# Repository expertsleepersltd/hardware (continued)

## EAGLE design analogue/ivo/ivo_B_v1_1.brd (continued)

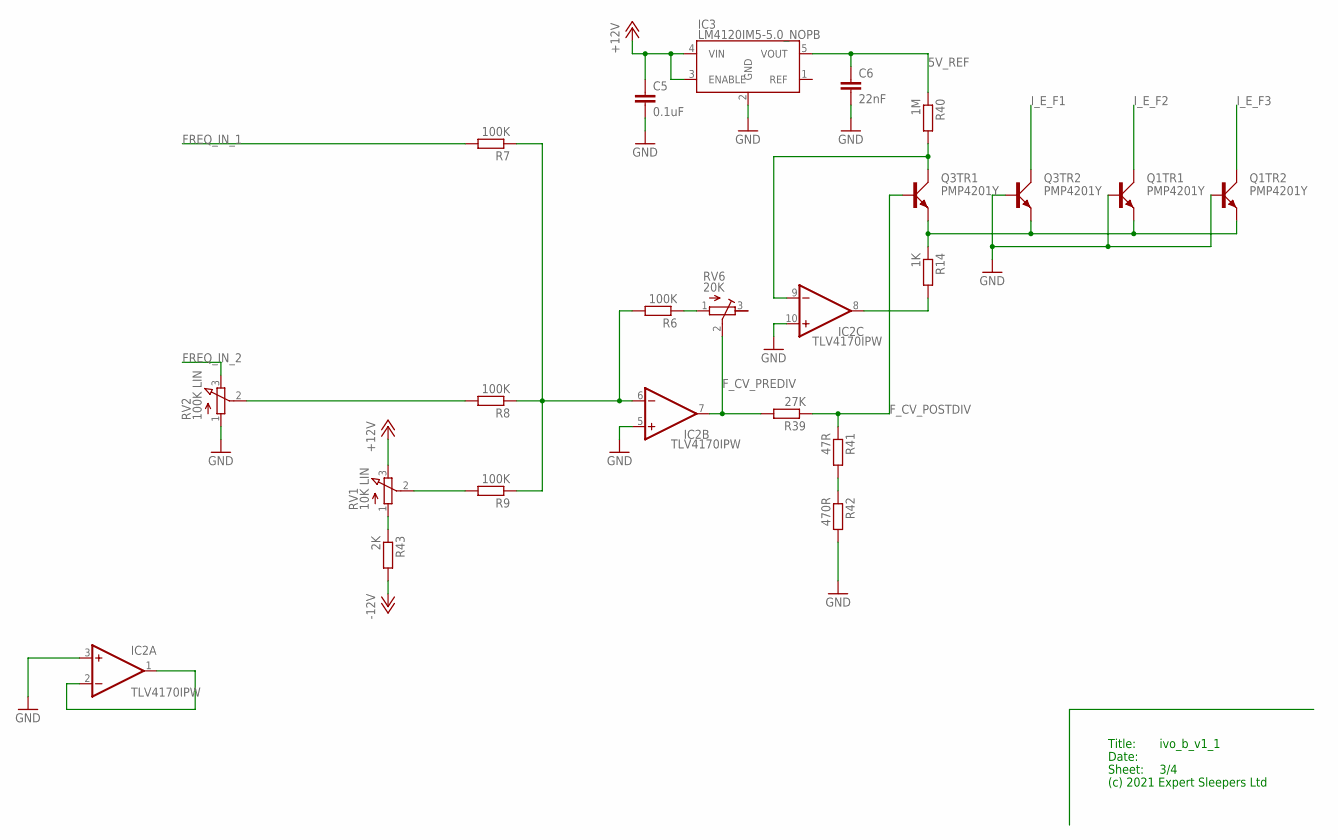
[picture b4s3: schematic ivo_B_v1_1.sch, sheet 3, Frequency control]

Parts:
C5: 0.1uF; C0402
C6: 22nF; C0402
IC2: TLV4170IPW; PW_R-PDSO-G14
IC3: LM4120IM5-5.0_NOPB; SOT95P280X145-5N
Q1, Q3: PMP4201Y; SOT65P210X110-6N
R6, R7, R8, R9: 100K; R0603
R14: 1K; R0603
R39: 27K; R0603
R40: 1M; R0603
R41: 47R; R0603
R42: 470R; R1206
R43: 2K; R0603
RV1: 10K LIN; RD1610NOA0X
RV2: 100K LIN; RD1610NOA0X
RV6: 20K; TC33X

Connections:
5V_REF: C6.1, IC3.5 (VOUT), R40.1
+12V: C5.1, IC3.3 (ENABLE), IC3.4 (VIN), RV1.3 (E); also elsewhere on the board
-12V: R43.2; also elsewhere on the board
FREQ_IN_1: R7.2; also elsewhere on the board
FREQ_IN_2: RV2.3 (E); also elsewhere on the board
F_CV_POSTDIV: Q3.1 (B), R39.1, R41.1
F_CV_PREDIV: IC2.7 (OUT), R39.2, RV6.2 (S)
GND: C5.2, C6.2, IC2.3 (+IN), IC2.5 (+IN), IC2.10 (+IN), IC3.2 (GND), Q1.1 (B), Q1.2 (B), Q3.2 (B), R42.2, RV2.1 (A); also elsewhere on the board
I_E_F1: Q3.3 (C); also elsewhere on the board
I_E_F2: Q1.6 (C); also elsewhere on the board
I_E_F3: Q1.3 (C); also elsewhere on the board
unnamed: R43.1, RV1.1 (A)
unnamed: R6.1, RV6.1 (A)
unnamed: IC2.6 (-IN), R6.2, R7.1, R8.1, R9.1
unnamed: IC2.1 (OUT), IC2.2 (-IN)
unnamed: R8.2, RV2.2 (S)
unnamed: R9.2, RV1.2 (S)
unnamed: R41.2, R42.1
unnamed: Q1.4 (E), Q1.5 (E), Q3.4 (E), Q3.5 (E), R14.1
unnamed: IC2.9 (-IN), Q3.6 (C), R40.2
unnamed: IC2.8 (OUT), R14.2

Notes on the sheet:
Title:
Date:
Sheet:
(c) 2021 Expert Sleepers Ltd

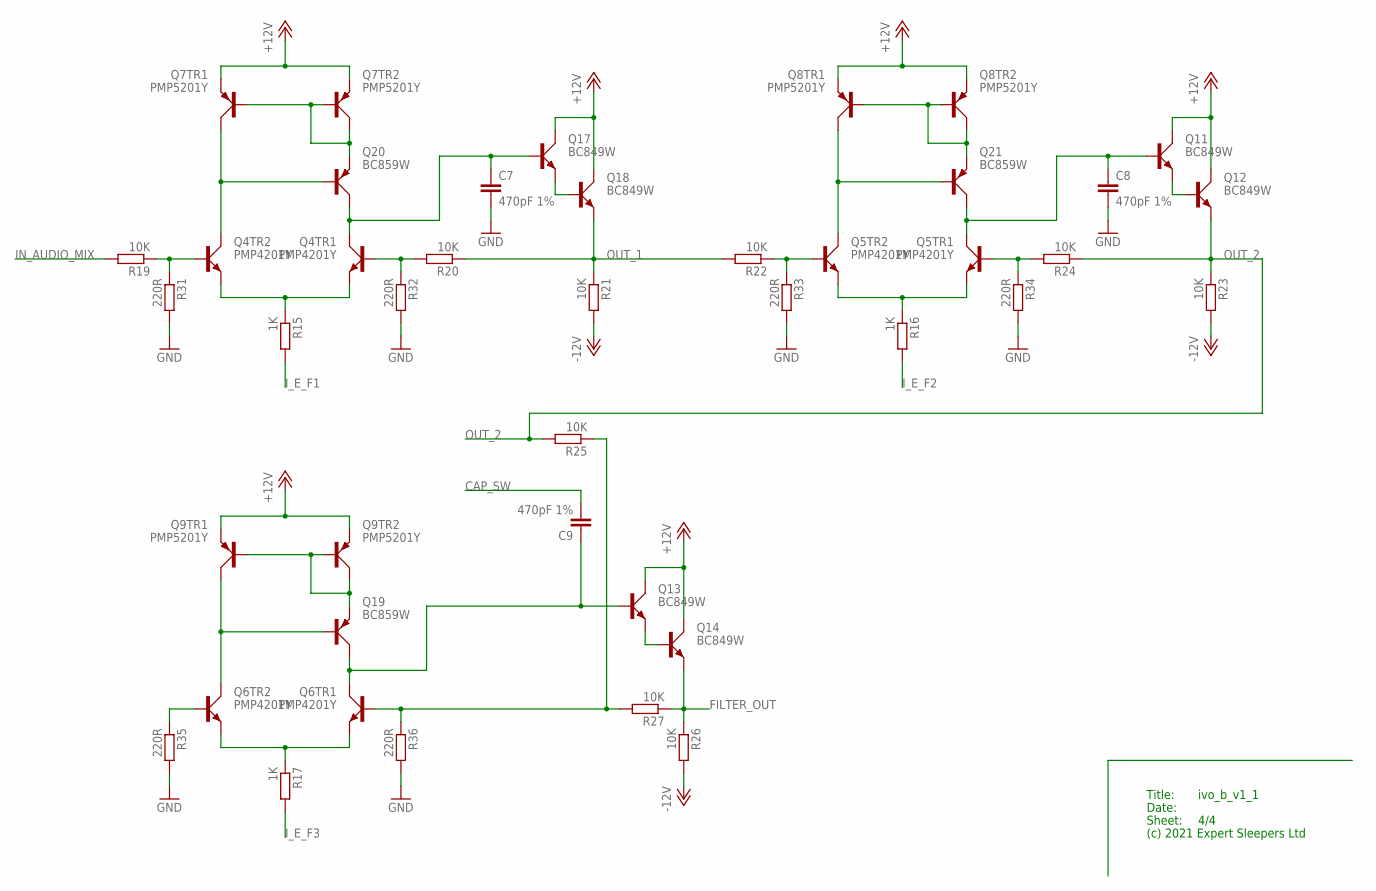
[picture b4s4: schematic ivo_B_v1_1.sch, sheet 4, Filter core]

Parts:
C7, C8, C9: 470pF 1%; C0603
Q4, Q5, Q6: PMP4201Y; SOT65P210X110-6N
Q7, Q8, Q9: PMP5201Y; SOT65P210X110-6N
Q11, Q12, Q13, Q14, Q17, Q18: BC849W; SOT323
Q19, Q20, Q21: BC859W; SOT323
R15, R16, R17: 1K; R0603
R19, R20, R21, R22, R23, R24, R25, R26, R27: 10K; R0603
R31, R32, R33, R34, R35, R36: 220R; R0603

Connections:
+12V: Q7.4 (E), Q7.5 (E), Q8.4 (E), Q8.5 (E), Q9.4 (E), Q9.5 (E), Q11.3 (C), Q12.3 (C), Q13.3 (C), Q14.3 (C), Q17.3 (C), Q18.3 (C); also elsewhere on the board
-12V: R21.2, R23.2, R26.2; also elsewhere on the board
CAP_SW: C9.2; also elsewhere on the board
FILTER_OUT: Q14.2 (E), R26.1, R27.1; also elsewhere on the board
GND: C7.2, C8.2, R31.2, R32.2, R33.2, R34.2, R35.2, R36.2; also elsewhere on the board
IN_AUDIO_MIX: R19.2; also elsewhere on the board
I_E_F1: R15.2; also elsewhere on the board
I_E_F2: R16.2; also elsewhere on the board
I_E_F3: R17.2; also elsewhere on the board
unnamed: Q4.2 (B), R19.1, R31.1
unnamed: Q4.4 (E), Q4.5 (E), R15.1
unnamed: C7.1, Q4.6 (C), Q17.1 (B), Q20.3 (C)
unnamed: Q4.3 (C), Q7.6 (C), Q20.1 (B)
unnamed: Q4.1 (B), R20.2, R32.1
unnamed: Q17.2 (E), Q18.1 (B)
unnamed: Q7.1 (B), Q7.2 (B), Q7.3 (C), Q20.2 (E)
unnamed: Q5.2 (B), R22.1, R33.1
unnamed: Q5.4 (E), Q5.5 (E), R16.1
unnamed: C8.1, Q5.6 (C), Q11.1 (B), Q21.3 (C)
unnamed: Q5.1 (B), R24.2, R34.1
unnamed: Q11.2 (E), Q12.1 (B)
unnamed: Q5.3 (C), Q8.6 (C), Q21.1 (B)
unnamed: Q8.1 (B), Q8.2 (B), Q8.3 (C), Q21.2 (E)
unnamed: Q6.2 (B), R35.1
unnamed: Q6.4 (E), Q6.5 (E), R17.1
unnamed: C9.1, Q6.6 (C), Q13.1 (B), Q19.3 (C)
unnamed: Q6.1 (B), R25.1, R27.2, R36.1
unnamed: Q13.2 (E), Q14.1 (B)
unnamed: Q6.3 (C), Q9.6 (C), Q19.1 (B)
unnamed: Q9.1 (B), Q9.2 (B), Q9.3 (C), Q19.2 (E)
OUT_1: Q18.2 (E), R20.1, R21.1, R22.2
OUT_2: Q12.2 (E), R23.1, R24.1, R25.2; also elsewhere on the board

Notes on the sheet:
Title:
Date:
Sheet:
(c) 2021 Expert Sleepers Ltd

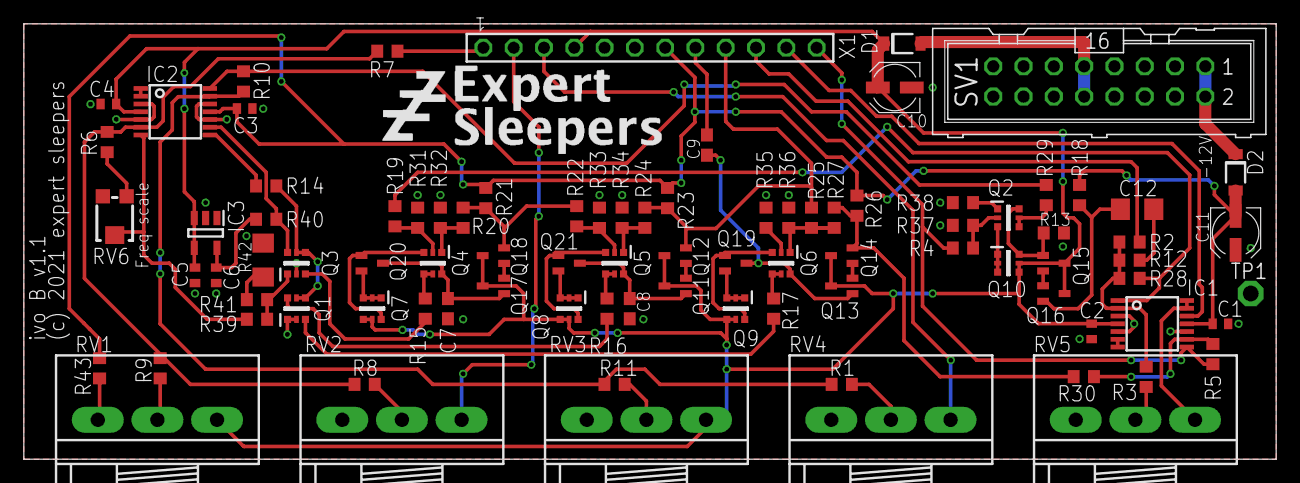
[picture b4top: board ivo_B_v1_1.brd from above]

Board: 2 copper layers, 105.0 x 36.5 mm, 91 parts (0 on the bottom side), 70 nets.

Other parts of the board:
U$1: ES_ZZZ_TEXT_TPLACE_1IN_600DPI

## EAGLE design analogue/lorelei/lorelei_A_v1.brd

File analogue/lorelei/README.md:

Lorelei
=====

https://expert-sleepers.co.uk/lorelei.html

Copyright (c) 2021 Expert Sleepers Ltd

Please refer to [LICENSE.md](LICENSE.md) for licensing information.

Please note that Expert Sleepers® is a registered trade mark in the UK. Remove any branding before making a derivative work.

Front panel layout is [here](../../panels).

Board and schematic are in [EAGLE](https://en.wikipedia.org/wiki/EAGLE_(program)) format.

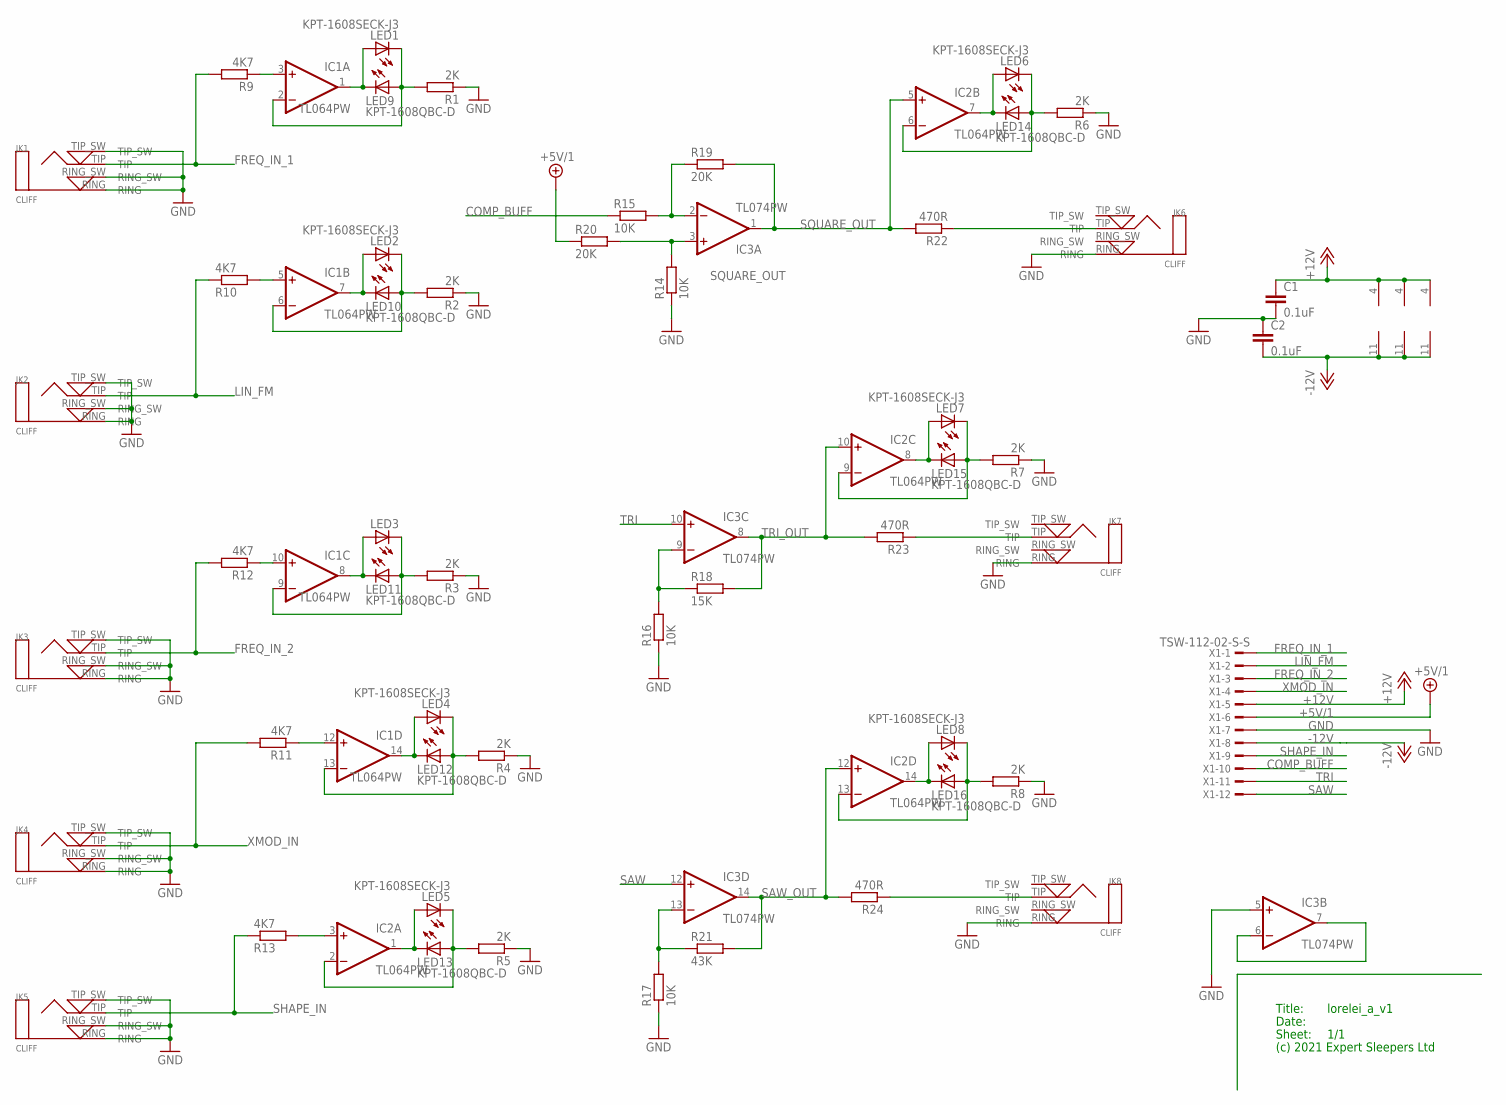
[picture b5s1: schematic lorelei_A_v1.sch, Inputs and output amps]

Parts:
C1, C2: 0.1uF; C0402
IC1, IC2: TL064PW; PW_R-PDSO-G14
IC3: TL074PW; PW_R-PDSO-G14
JK1, JK2, JK3, JK4, JK5, JK6, JK7, JK8: CLIFF; CLIFF3.5MMPCB
LED1, LED2, LED3, LED4, LED5, LED6, LED7, LED8: KPT-1608SECK-J3; CHIPLED_0603_LEFT
LED9, LED10, LED11, LED12, LED13, LED14, LED15, LED16: KPT-1608QBC-D; CHIPLED_0603_RIGHT
R1, R2, R3, R4, R5, R6, R7, R8: 2K; R1206
R9, R10, R11, R12, R13: 4K7; R1206
R14, R15, R16, R17: 10K; R0603
R18: 15K; R0603
R19, R20: 20K; R0603
R21: 43K; R0603
R22, R23, R24: 470R; R1206
X1: TSW-112-02-S-S

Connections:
+5V/1: R20.1, X1.6
+12V: C1.1, IC1.4 (V+), IC2.4 (V+), IC3.4 (V+), X1.5
-12V: C2.2, IC1.11 (V-), IC2.11 (V-), IC3.11 (V-), X1.8
COMP_BUFF: R15.1, X1.10
FREQ_IN_1: JK1.TIP, R9.2, X1.1
FREQ_IN_2: JK3.TIP, R12.2, X1.3
GND: C1.2, C2.1, IC3.5 (+IN), JK1.RING, JK1.RING_SW, JK1.TIP_SW, JK2.RING, JK2.RING_SW, JK2.TIP_SW, JK3.RING, JK3.RING_SW, JK3.TIP_SW, JK4.RING, JK4.RING_SW, JK4.TIP_SW, JK5.RING, JK5.RING_SW, JK5.TIP_SW, JK6.RING, JK7.RING, JK8.RING, R1.1, R2.1, R3.1, R4.1, R5.1, R6.1, R7.1, R8.1, R14.1, R16.1, R17.1, X1.7
LIN_FM: JK2.TIP, R10.1, X1.2
unnamed: IC3.6 (-IN), IC3.7 (OUT)
unnamed: IC3.3 (+IN), R14.2, R20.2
unnamed: IC3.2 (-IN), R15.2, R19.1
unnamed: IC3.9 (-IN), R16.2, R18.1
unnamed: IC3.13 (-IN), R17.2, R21.1
unnamed: JK7.TIP, R23.1
unnamed: IC1.12 (+IN), R11.1
unnamed: IC1.14 (OUT), LED4.2 (A), LED12.2 (C)
unnamed: IC1.13 (-IN), LED4.1 (C), LED12.1 (A), R4.2
unnamed: IC1.1 (OUT), LED1.2 (A), LED9.2 (C)
unnamed: IC1.2 (-IN), LED1.1 (C), LED9.1 (A), R1.2
unnamed: IC2.3 (+IN), R13.2
unnamed: IC1.8 (OUT), LED3.2 (A), LED11.2 (C)
unnamed: IC1.9 (-IN), LED3.1 (C), LED11.1 (A), R3.2
unnamed: IC1.3 (+IN), R9.1
unnamed: IC1.10 (+IN), R12.1
unnamed: IC1.7 (OUT), LED2.2 (A), LED10.2 (C)
unnamed: IC1.6 (-IN), LED2.1 (C), LED10.1 (A), R2.2
unnamed: IC2.7 (OUT), LED6.2 (A), LED14.2 (C)
unnamed: IC2.6 (-IN), LED6.1 (C), LED14.1 (A), R6.2
unnamed: JK6.TIP, R22.1
unnamed: IC2.8 (OUT), LED7.2 (A), LED15.2 (C)
unnamed: IC2.9 (-IN), LED7.1 (C), LED15.1 (A), R7.2
unnamed: IC2.14 (OUT), LED8.2 (A), LED16.2 (C)
unnamed: IC2.13 (-IN), LED8.1 (C), LED16.1 (A), R8.2
unnamed: IC2.1 (OUT), LED5.2 (A), LED13.2 (C)
unnamed: IC2.2 (-IN), LED5.1 (C), LED13.1 (A), R5.2
unnamed: JK8.TIP, R24.1
OUT_TO_FB1: IC1.5 (+IN), R10.2
SAW: IC3.12 (+IN), X1.12
SAW_OUT: IC2.12 (+IN), IC3.14 (OUT), R21.2, R24.2
SHAPE_IN: JK5.TIP, R13.1, X1.9
SQUARE_OUT: IC2.5 (+IN), IC3.1 (OUT), R19.2, R22.2
TRI: IC3.10 (+IN), X1.11
TRI_OUT: IC2.10 (+IN), IC3.8 (OUT), R18.2, R23.2
XMOD_IN: JK4.TIP, R11.2, X1.4

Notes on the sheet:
Title:
Date:
Sheet:
(c) 2021 Expert Sleepers Ltd

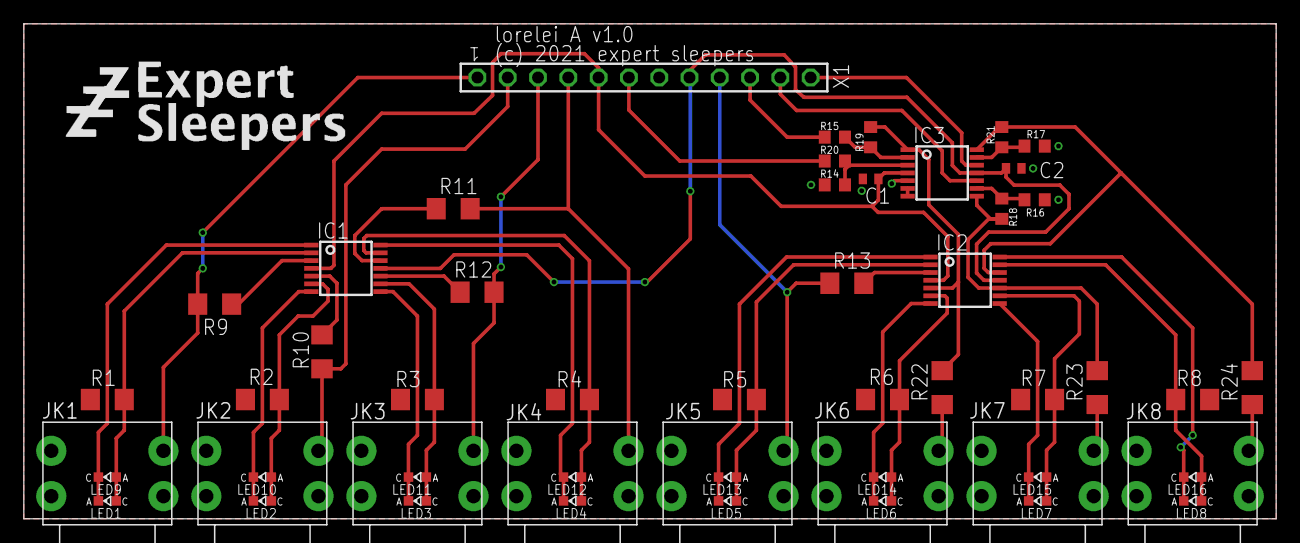
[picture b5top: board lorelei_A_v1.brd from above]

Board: 2 copper layers, 105.0 x 41.5 mm, 55 parts (0 on the bottom side), 44 nets.

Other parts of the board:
U$1: ES_ZZZ_TEXT_TPLACE_1IN_600DPI

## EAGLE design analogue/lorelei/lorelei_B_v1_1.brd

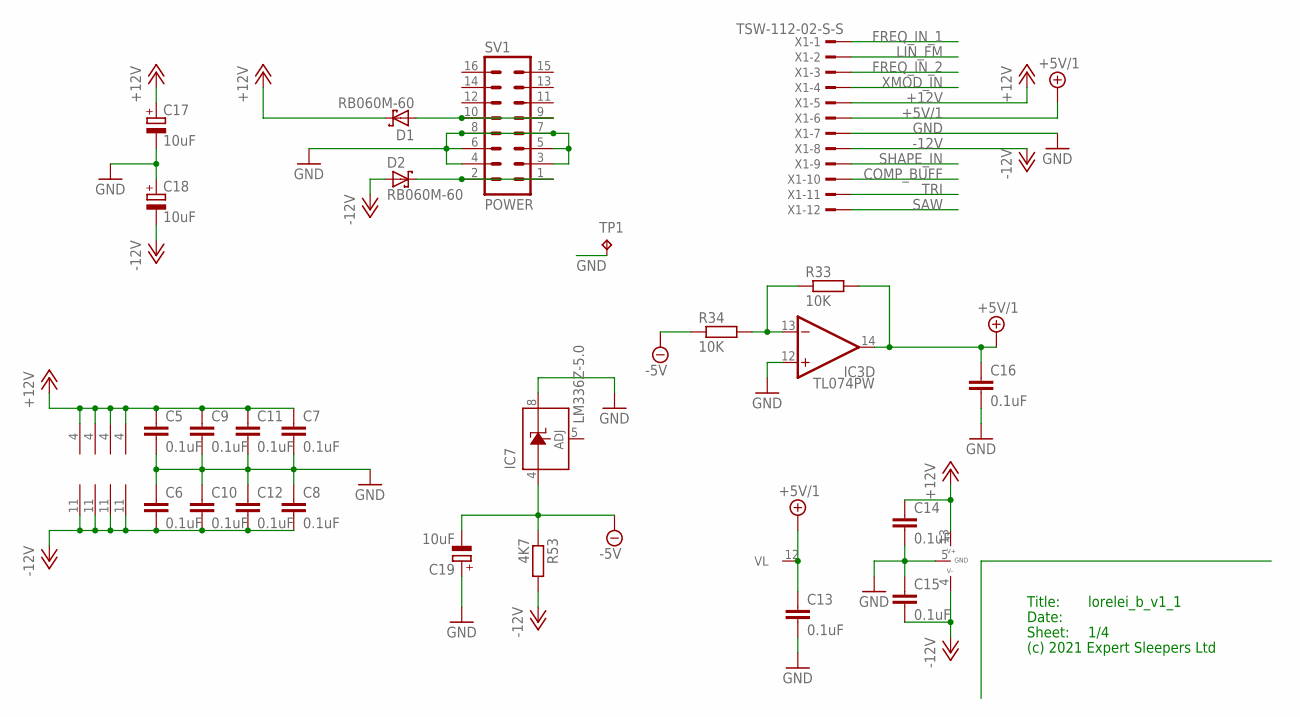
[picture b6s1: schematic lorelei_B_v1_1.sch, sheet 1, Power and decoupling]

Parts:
C5, C6, C7, C8, C9, C10, C11, C12, C13, C14, C15, C16: 0.1uF; C0402
C17, C18, C19: 10uF; UD-4X5,8_NICHICON
D1, D2: RB060M-60; SOD123FL
IC1, IC2, IC3, IC4: TL074PW; PW_R-PDSO-G14
IC7: LM336Z-5.0; SO08
IC8: DG211BDY; SO16
R33, R34: 10K; R0603
R53: 4K7; R0603
SV1: POWER; ML16
TP1: RA2; P1-13
X1: TSW-112-02-S-S

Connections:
+5V/1: C13.1, C16.1, IC3.14 (OUT), IC8.12 (VL), R33.2, X1.6; also elsewhere on the board
+12V: C5.1, C7.1, C9.1, C11.1, C14.1, C17.+, D1.C, IC1.4 (V+), IC2.4 (V+), IC3.4 (V+), IC4.4 (V+), IC8.13 (V+), X1.5; also elsewhere on the board
-5V: C19.-, IC7.4 (A), R34.1, R53.1; also elsewhere on the board
-12V: C6.2, C8.2, C10.2, C12.2, C15.2, C18.-, D2.A, IC1.11 (V-), IC2.11 (V-), IC3.11 (V-), IC4.11 (V-), IC8.4 (V-), R53.2, X1.8; also elsewhere on the board
COMP_BUFF: X1.10; also elsewhere on the board
FREQ_IN_1: X1.1; also elsewhere on the board
FREQ_IN_2: X1.3; also elsewhere on the board
GND: C5.2, C6.1, C7.2, C8.1, C9.2, C10.1, C11.2, C12.1, C13.2, C14.2, C15.1, C16.2, C17.-, C18.+, C19.+, IC3.12 (+IN), IC7.8 (C), IC8.5 (GND), SV1.3, SV1.4, SV1.5, SV1.6, SV1.7, SV1.8, TP1.TP, X1.7; also elsewhere on the board
LIN_FM: X1.2; also elsewhere on the board
unnamed: D2.C, SV1.1, SV1.2
unnamed: D1.A, SV1.9, SV1.10
unnamed: IC3.13 (-IN), R33.1, R34.2
SAW: X1.12; also elsewhere on the board
SHAPE_IN: X1.9; also elsewhere on the board
TRI: X1.11; also elsewhere on the board
XMOD_IN: X1.4; also elsewhere on the board

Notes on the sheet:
Title:
Date:
Sheet:
(c) 2021 Expert Sleepers Ltd

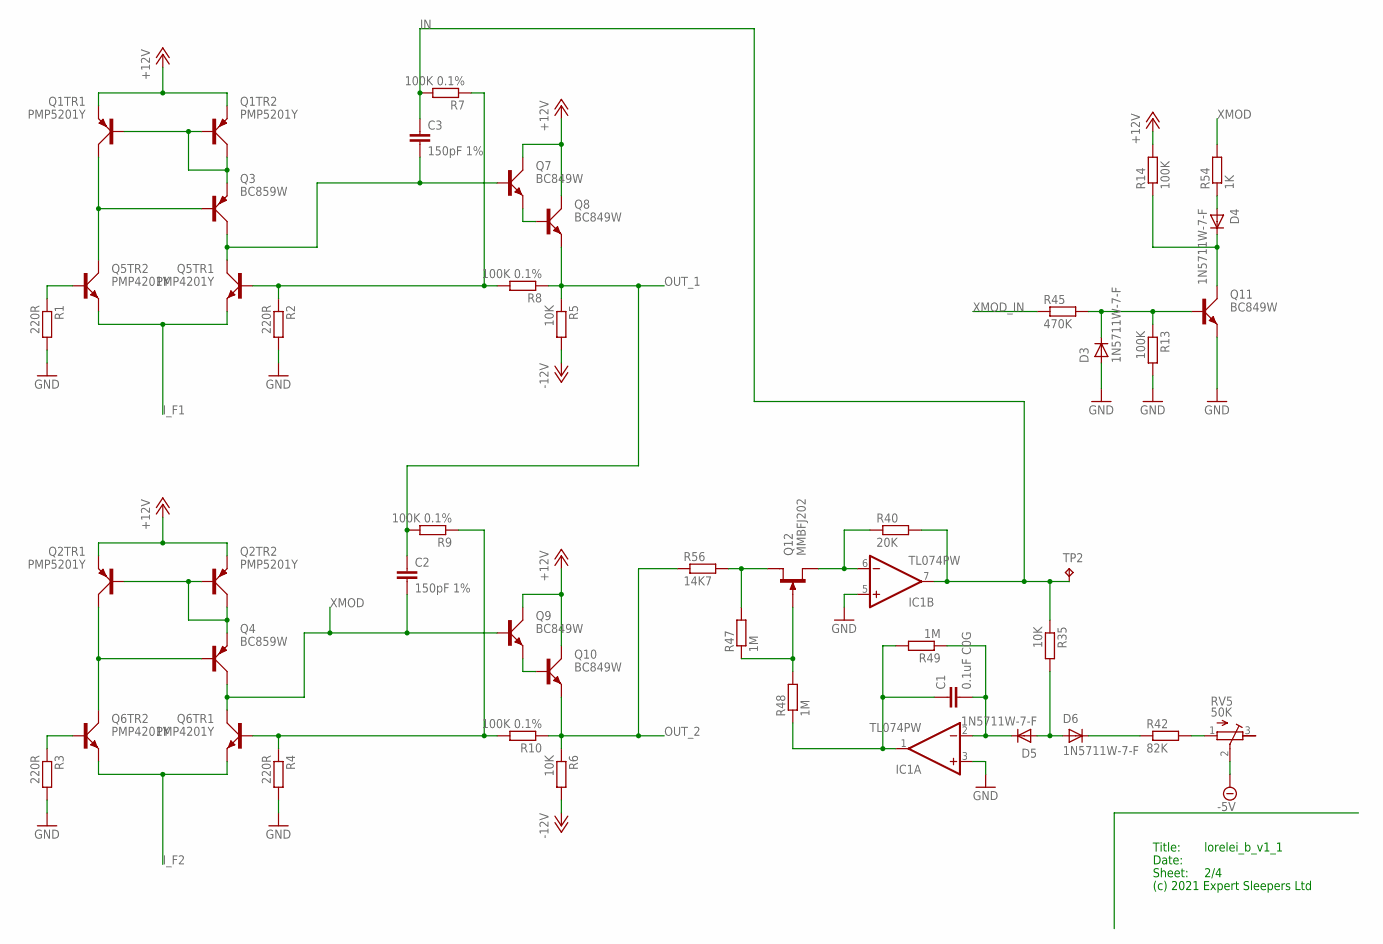
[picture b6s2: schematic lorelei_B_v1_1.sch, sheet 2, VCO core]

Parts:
C1: 0.1uF C0G; C1206
C2, C3: 150pF 1%; C0805
D3, D4, D5, D6: 1N5711W-7-F; SOD123
IC1: TL074PW; PW_R-PDSO-G14
Q1, Q2: PMP5201Y; SOT65P210X110-6N
Q3, Q4: BC859W; SOT323
Q5, Q6: PMP4201Y; SOT65P210X110-6N
Q7, Q8, Q9, Q10, Q11: BC849W; SOT323
Q12: MMBFJ202; SOT23
R1, R2, R3, R4: 220R; R0603
R5, R6, R35: 10K; R0603
R7, R8, R9, R10: 100K 0.1%; R0603
R13, R14: 100K; R0603
R40: 20K; R0603
R42: 82K; R0603
R45: 470K; R0603
R47, R48, R49: 1M; R0603
R54: 1K; R0603
R56: 14K7; R0603
RV5: 50K; TC33X
TP2: RA2; P1-13

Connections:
+12V: Q1.4 (E), Q1.5 (E), Q2.4 (E), Q2.5 (E), Q7.3 (C), Q8.3 (C), Q9.3 (C), Q10.3 (C), R14.2; also elsewhere on the board
-5V: RV5.2 (S); also elsewhere on the board
-12V: R5.2, R6.2; also elsewhere on the board
GND: D3.A, IC1.3 (+IN), IC1.5 (+IN), Q11.2 (E), R1.2, R2.2, R3.2, R4.2, R13.2; also elsewhere on the board
IN: C3.1, IC1.7 (OUT), R7.2, R35.1, R40.2, TP2.TP; also elsewhere on the board
I_F1: Q5.4 (E), Q5.5 (E); also elsewhere on the board
I_F2: Q6.4 (E), Q6.5 (E); also elsewhere on the board
JFET_D: Q12.1 (D), R47.2, R56.2
JFET_G: Q12.3 (G), R47.1, R48.2
JFET_S: IC1.6 (-IN), Q12.2 (S), R40.1
unnamed: D3.C, Q11.1 (B), R13.1, R45.2
unnamed: D4.C, Q11.3 (C), R14.1
unnamed: D4.A, R54.1
unnamed: C1.2, D5.C, IC1.2 (-IN), R49.1
unnamed: R42.2, RV5.1 (A)
unnamed: D5.A, D6.A, R35.2
unnamed: C1.1, IC1.1 (OUT), R48.1, R49.2
unnamed: Q5.2 (B), R1.1
unnamed: C3.2, Q3.3 (C), Q5.6 (C), Q7.1 (B)
unnamed: Q5.1 (B), R2.1, R7.1, R8.2
unnamed: D6.C, R42.1
unnamed: Q7.2 (E), Q8.1 (B)
unnamed: Q1.6 (C), Q3.1 (B), Q5.3 (C)
unnamed: Q1.1 (B), Q1.2 (B), Q1.3 (C), Q3.2 (E)
unnamed: Q6.2 (B), R3.1
unnamed: Q6.1 (B), R4.1, R9.1, R10.2
unnamed: Q9.2 (E), Q10.1 (B)
unnamed: Q2.6 (C), Q4.1 (B), Q6.3 (C)
unnamed: Q2.1 (B), Q2.2 (B), Q2.3 (C), Q4.2 (E)
OUT_1: C2.1, Q8.2 (E), R5.1, R8.1, R9.2; also elsewhere on the board
OUT_2: Q10.2 (E), R6.1, R10.1, R56.1
XMOD: C2.2, Q4.3 (C), Q6.6 (C), Q9.1 (B), R54.2
XMOD_IN: R45.1; also elsewhere on the board

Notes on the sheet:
Title:
Date:
Sheet:
(c) 2021 Expert Sleepers Ltd

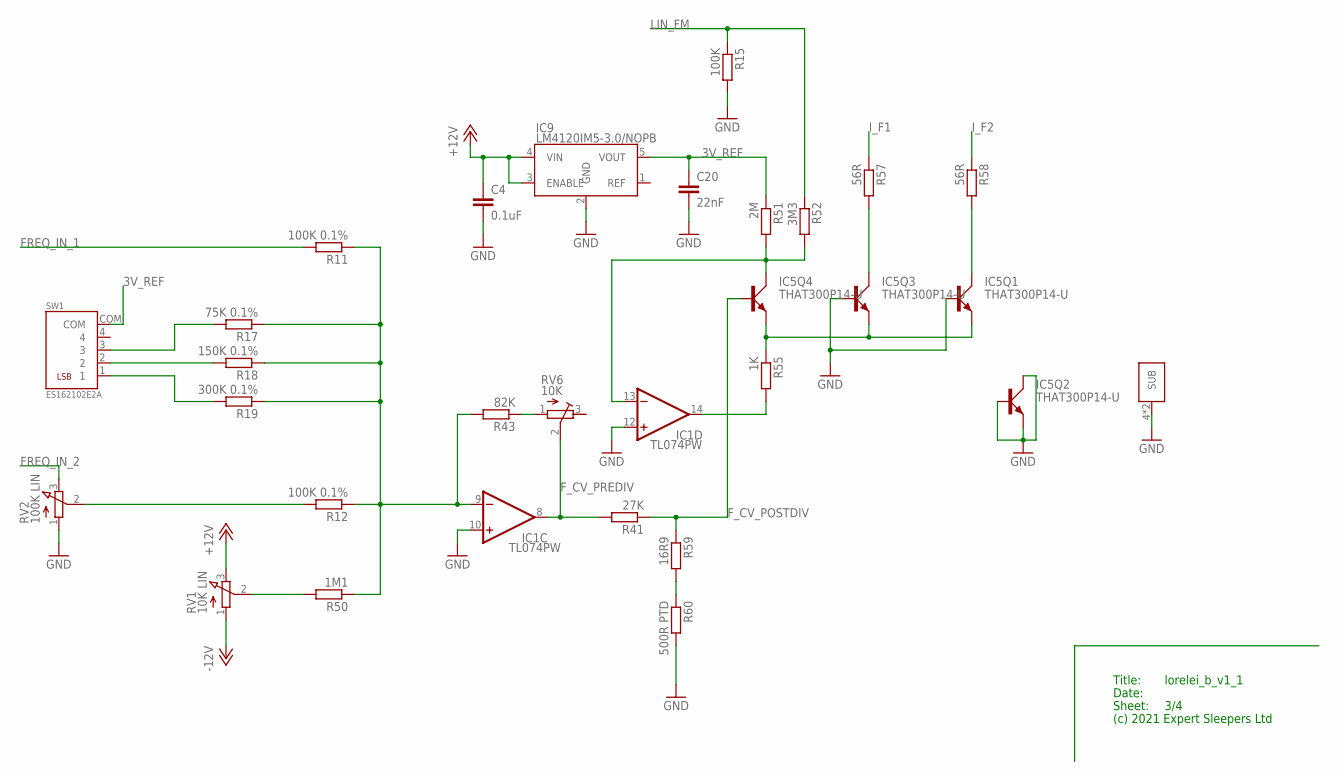
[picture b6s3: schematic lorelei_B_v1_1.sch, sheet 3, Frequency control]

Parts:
C4: 0.1uF; C0402
C20: 22nF; C0402
IC1: TL074PW; PW_R-PDSO-G14
IC5: THAT300P14-U; DIL14
IC9: LM4120IM5-3.0/NOPB; SOT95P280X145-5N
R11, R12: 100K 0.1%; R0603
R15: 100K; R0603
R17: 75K 0.1%; R0603
R18: 150K 0.1%; R0603
R19: 300K 0.1%; R0603
R41: 27K; R0603
R43: 82K; R0603
R50: 1M1; R0603
R51: 2M; R0603
R52: 3M3; R0603
R55: 1K; R0603
R57, R58: 56R; R0603
R59: 16R9; R0603
R60: 500R PTD; R0805
RV1: 10K LIN; RD1610NOA0X
RV2: 100K LIN; RD1610NOA0X
RV6: 10K; RTRIM3296W
SW1: ES162102E2A

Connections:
3V_REF: C20.1, IC9.5 (VOUT), R51.1, SW1.COM
+12V: C4.1, IC9.3 (ENABLE), IC9.4 (VIN), RV1.3 (E); also elsewhere on the board
-12V: RV1.1 (A); also elsewhere on the board
FREQ_IN_1: R11.2; also elsewhere on the board
FREQ_IN_2: RV2.3 (E); also elsewhere on the board
F_CV_POSTDIV: IC5.9 (B), R41.1, R59.1
F_CV_PREDIV: IC1.8 (OUT), R41.2, RV6.2 (S)
GND: C4.2, C20.2, IC1.10 (+IN), IC1.12 (+IN), IC5.2 (B), IC5.4 (SUB), IC5.6 (B), IC5.11 (SUB), IC5.12 (E), IC5.13 (B), IC5.14 (C), IC9.2 (GND), R15.2, R60.2, RV2.1 (A); also elsewhere on the board
I_E_F1: IC5.7 (C), R57.2
I_E_F2: IC5.1 (C), R58.2
I_F1: R57.1; also elsewhere on the board
I_F2: R58.1; also elsewhere on the board
LIN_FM: R15.1, R52.1; also elsewhere on the board
unnamed: R19.2, SW1.1
unnamed: R43.1, RV6.1 (A)
unnamed: IC1.9 (-IN), R11.1, R12.1, R17.1, R18.1, R19.1, R43.2, R50.1
unnamed: R18.2, SW1.2
unnamed: R17.2, SW1.3
unnamed: R12.2, RV2.2 (S)
unnamed: R50.2, RV1.2 (S)
unnamed: R59.2, R60.1
unnamed: IC5.3 (E), IC5.5 (E), IC5.10 (E), R55.1
unnamed: IC1.13 (-IN), IC5.8 (C), R51.2, R52.2
unnamed: IC1.14 (OUT), R55.2

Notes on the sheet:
Title:
Date:
Sheet:
(c) 2021 Expert Sleepers Ltd

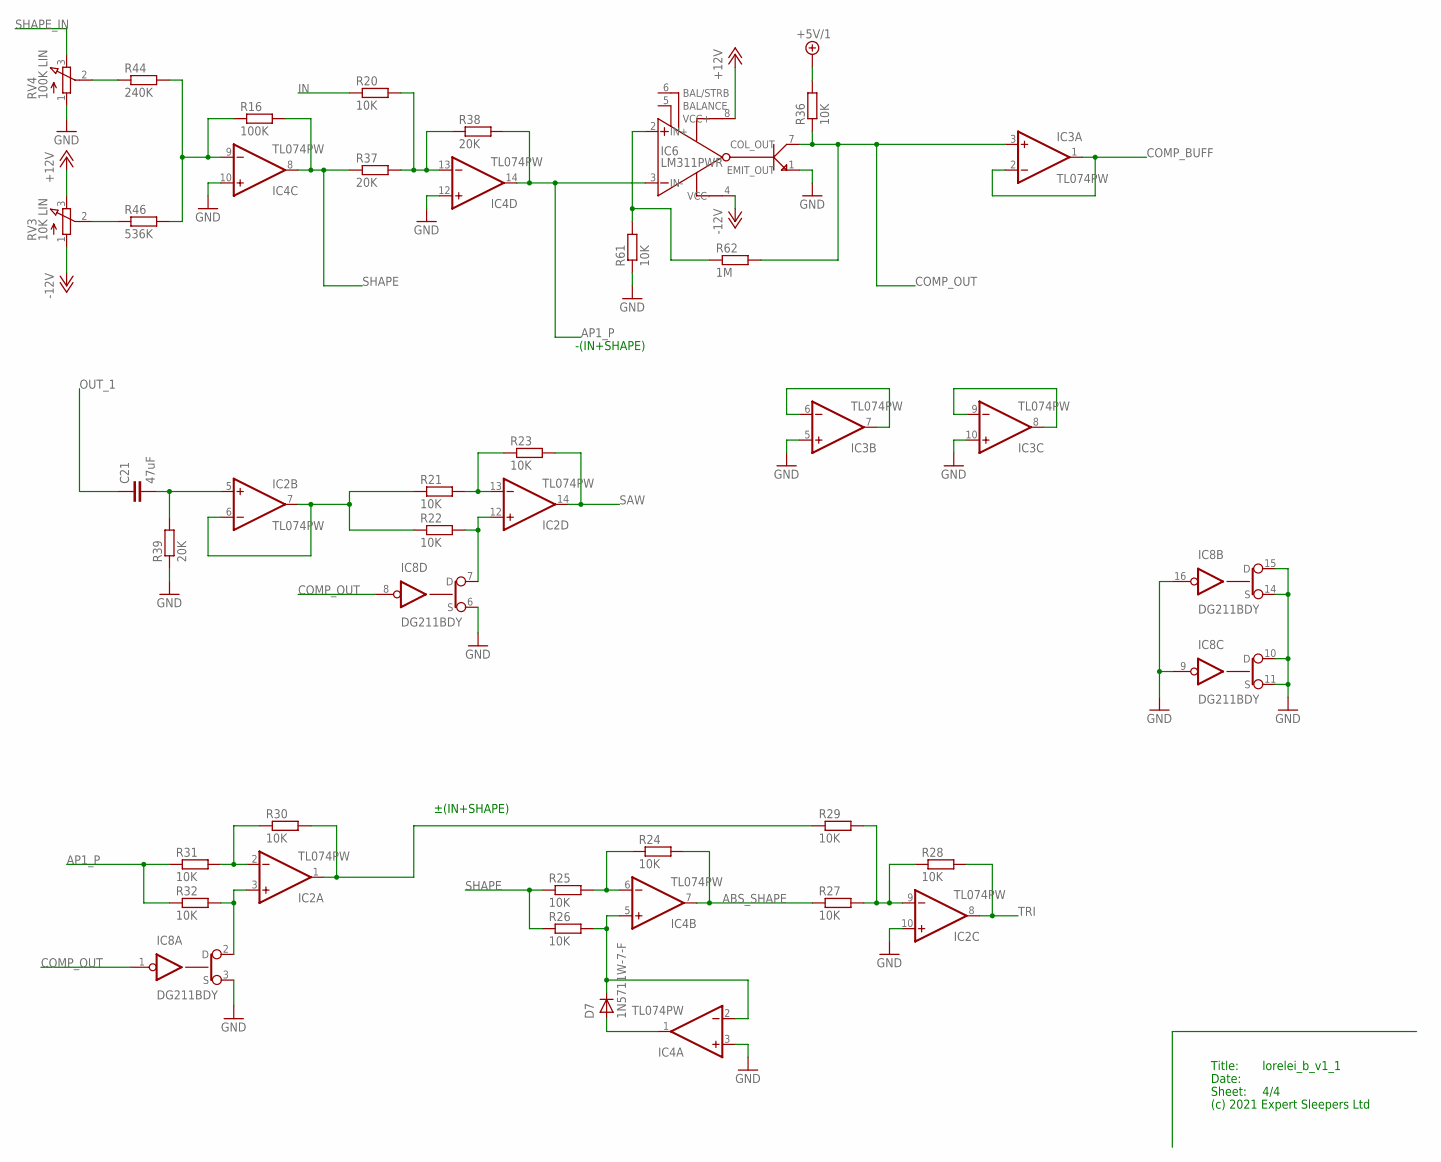
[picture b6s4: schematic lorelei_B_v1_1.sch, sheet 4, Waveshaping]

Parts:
C21: 47uF; C1206
D7: 1N5711W-7-F; SOD123
IC2, IC3, IC4: TL074PW; PW_R-PDSO-G14
IC6: LM311PWR; SOP65P640X120-8N
IC8: DG211BDY; SO16
R16: 100K; R0603
R20, R21, R22, R23, R24, R25, R26, R27, R28, R29, R30, R31, R32, R36, R61: 10K; R0603
R37, R38, R39: 20K; R0603
R44: 240K; R0603
R46: 536K; R0603
R62: 1M; R0603
RV3: 10K LIN; RD1610NOA0X
RV4: 100K LIN; RD1610NOA0X

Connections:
+5V/1: R36.2; also elsewhere on the board
+12V: IC6.8 (VCC+), RV3.3 (E); also elsewhere on the board
-12V: IC6.4 (VCC-), RV3.1 (A); also elsewhere on the board
ABS_SHAPE: IC4.7 (OUT), R24.2, R27.1
AP1_P: IC4.14 (OUT), IC6.3 (IN-), R31.1, R32.1, R38.2
COMP_BUFF: IC3.1 (OUT), IC3.2 (-IN); also elsewhere on the board
COMP_OUT: IC3.3 (+IN), IC6.7 (COL_OUT), IC8.1 (IN), IC8.8 (IN), R36.1, R62.2
GND: IC2.10 (+IN), IC3.5 (+IN), IC3.10 (+IN), IC4.3 (+IN), IC4.10 (+IN), IC4.12 (+IN), IC6.1 (EMIT_OUT), IC8.3 (S), IC8.6 (S), IC8.9 (IN), IC8.10 (D), IC8.11 (S), IC8.14 (S), IC8.15 (D), IC8.16 (IN), R39.1, R61.1, RV4.1 (A); also elsewhere on the board
IN: R20.1; also elsewhere on the board
unnamed: IC6.2 (IN+), R61.2, R62.1
unnamed: R46.1, RV3.2 (S)
unnamed: C21.2, IC2.5 (+IN), R39.2
unnamed: IC4.9 (-IN), R16.1, R44.2, R46.2
unnamed: IC4.6 (-IN), R24.1, R25.2
unnamed: IC4.13 (-IN), R20.2, R37.2, R38.1
unnamed: D7.C, IC4.2 (-IN), IC4.5 (+IN), R26.2
unnamed: IC2.6 (-IN), IC2.7 (OUT), R21.1, R22.1
unnamed: IC2.13 (-IN), R21.2, R23.1
unnamed: IC2.12 (+IN), IC8.7 (D), R22.2
unnamed: D7.A, IC4.1 (OUT)
unnamed: IC2.2 (-IN), R30.1, R31.2
unnamed: IC2.9 (-IN), R27.2, R28.1, R29.2
unnamed: IC2.1 (OUT), R29.1, R30.2
unnamed: IC2.3 (+IN), IC8.2 (D), R32.2
unnamed: R44.1, RV4.2 (S)
unnamed: IC3.6 (-IN), IC3.7 (OUT)
unnamed: IC3.8 (OUT), IC3.9 (-IN)
OUT_1: C21.1; also elsewhere on the board
SAW: IC2.14 (OUT), R23.2; also elsewhere on the board
SHAPE: IC4.8 (OUT), R16.2, R25.1, R26.1, R37.1
SHAPE_IN: RV4.3 (E); also elsewhere on the board
TRI: IC2.8 (OUT), R28.2; also elsewhere on the board

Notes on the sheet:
-(IN+SHAPE)
±(IN+SHAPE)
Title:
Date:
Sheet:
(c) 2021 Expert Sleepers Ltd

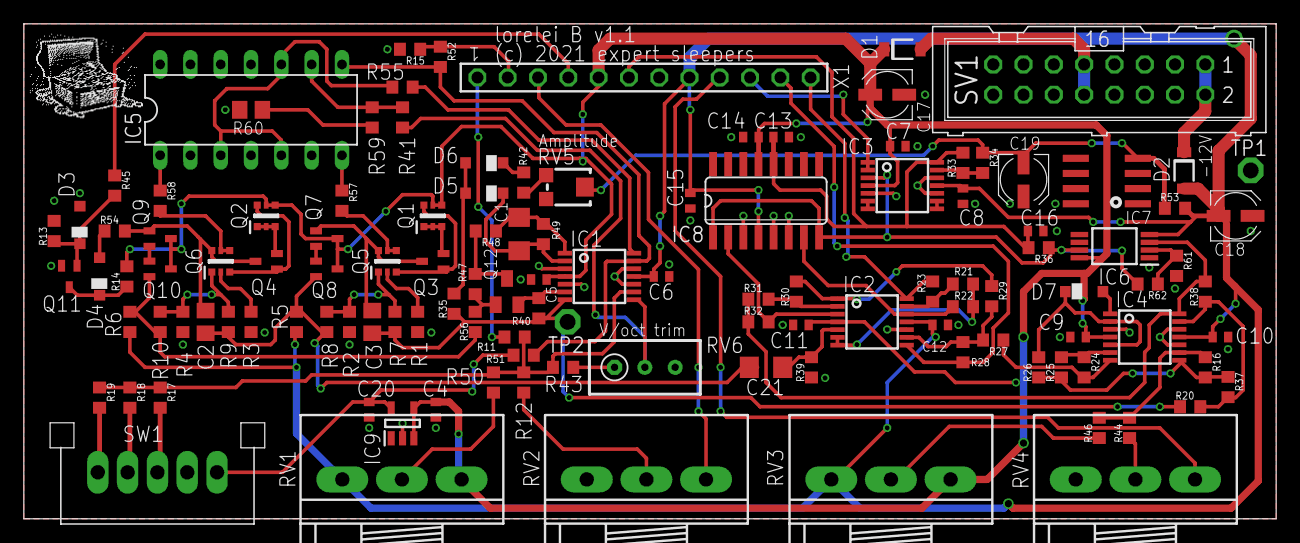
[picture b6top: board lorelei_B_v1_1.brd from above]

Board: 2 copper layers, 105.0 x 41.5 mm, 123 parts (0 on the bottom side), 82 nets.

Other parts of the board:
U$3: TREASURE_10MM_300DPI

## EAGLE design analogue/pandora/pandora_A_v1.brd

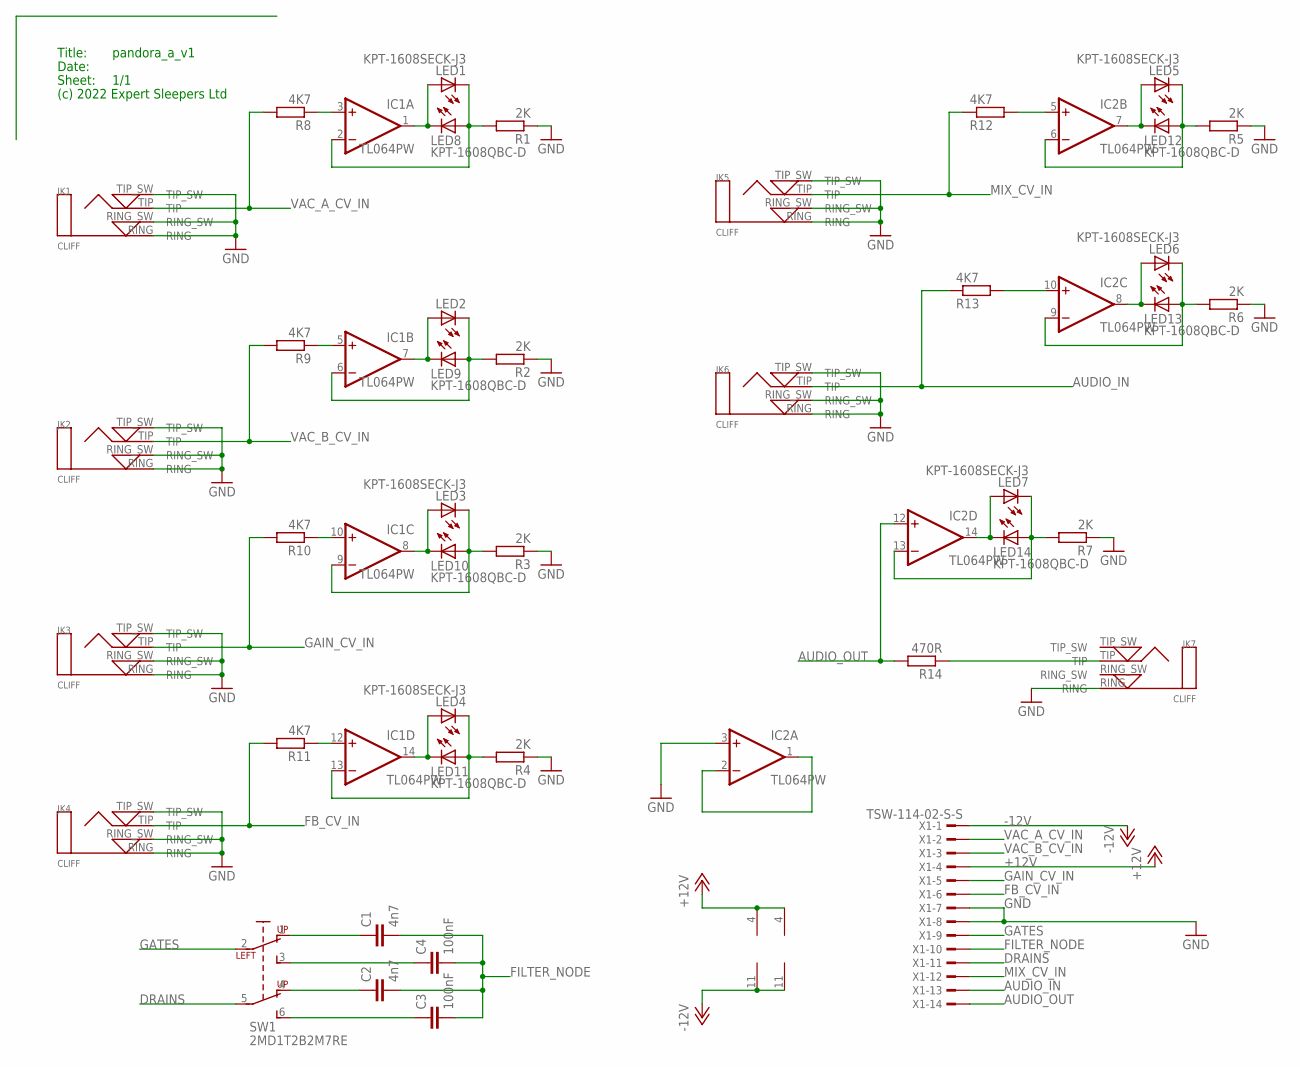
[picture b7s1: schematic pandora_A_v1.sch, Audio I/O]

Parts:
C1, C2: 4n7; C0805
C3, C4: 100nF; C1206
IC1, IC2: TL064PW; PW_R-PDSO-G14
JK1, JK2, JK3, JK4, JK5, JK6, JK7: CLIFF; CLIFF3.5MMPCB
LED1, LED2, LED3, LED4, LED5, LED6, LED7: KPT-1608SECK-J3; CHIPLED_0603_LEFT
LED8, LED9, LED10, LED11, LED12, LED13, LED14: KPT-1608QBC-D; CHIPLED_0603_RIGHT
R1, R2, R3, R4, R5, R6, R7: 2K; R1206
R8, R9, R10, R11, R12, R13: 4K7; R1206
R14: 470R; R1206
SW1: 2MD1T2B2M7RE
X1: TSW-114-02-S-S

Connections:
+12V: IC1.4 (V+), IC2.4 (V+), X1.4
-12V: IC1.11 (V-), IC2.11 (V-), X1.1
AUDIO_IN: JK6.TIP, R13.1, X1.13
AUDIO_OUT: IC2.12 (+IN), R14.2, X1.14
DRAINS: SW1.5 (PR), X1.11
FB_CV_IN: JK4.TIP, R11.2, X1.6
FILTER_NODE: C1.2, C2.2, C3.2, C4.2, X1.10
GAIN_CV_IN: JK3.TIP, R10.2, X1.5
GATES: SW1.2 (PL), X1.9
GND: IC2.3 (+IN), JK1.RING, JK1.RING_SW, JK1.TIP_SW, JK2.RING, JK2.RING_SW, JK2.TIP_SW, JK3.RING, JK3.RING_SW, JK3.TIP_SW, JK4.RING, JK4.RING_SW, JK4.TIP_SW, JK5.RING, JK5.RING_SW, JK5.TIP_SW, JK6.RING, JK6.RING_SW, JK6.TIP_SW, JK7.RING, R1.1, R2.1, R3.1, R4.1, R5.1, R6.1, R7.1, X1.7, X1.8
MIX_CV_IN: JK5.TIP, R12.1, X1.12
unnamed: IC1.10 (+IN), R10.1
unnamed: IC1.13 (-IN), LED4.1 (C), LED11.1 (A), R4.2
unnamed: IC1.14 (OUT), LED4.2 (A), LED11.2 (C)
unnamed: IC2.1 (OUT), IC2.2 (-IN)
unnamed: IC1.12 (+IN), R11.1
unnamed: IC1.8 (OUT), LED3.2 (A), LED10.2 (C)
unnamed: IC1.5 (+IN), R9.1
unnamed: IC1.9 (-IN), LED3.1 (C), LED10.1 (A), R3.2
unnamed: IC1.1 (OUT), LED1.2 (A), LED8.2 (C)
unnamed: IC2.10 (+IN), R13.2
unnamed: IC1.2 (-IN), LED1.1 (C), LED8.1 (A), R1.2
unnamed: IC1.3 (+IN), R8.1
unnamed: IC1.7 (OUT), LED2.2 (A), LED9.2 (C)
unnamed: IC1.6 (-IN), LED2.1 (C), LED9.1 (A), R2.2
unnamed: IC2.5 (+IN), R12.2
unnamed: IC2.8 (OUT), LED6.2 (A), LED13.2 (C)
unnamed: IC2.9 (-IN), LED6.1 (C), LED13.1 (A), R6.2
unnamed: IC2.14 (OUT), LED7.2 (A), LED14.2 (C)
unnamed: IC2.13 (-IN), LED7.1 (C), LED14.1 (A), R7.2
unnamed: IC2.7 (OUT), LED5.2 (A), LED12.2 (C)
unnamed: IC2.6 (-IN), LED5.1 (C), LED12.1 (A), R5.2
unnamed: JK7.TIP, R14.1
unnamed: C1.1, SW1.1 (LU)
unnamed: C2.1, SW1.4 (RU)
unnamed: C4.1, SW1.3 (LD)
unnamed: C3.1, SW1.6 (RD)
VAC_A_CV_IN: JK1.TIP, R8.2, X1.2
VAC_B_CV_IN: JK2.TIP, R9.2, X1.3

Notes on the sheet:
Title:
Date:
Sheet:
(c) 2022 Expert Sleepers Ltd
